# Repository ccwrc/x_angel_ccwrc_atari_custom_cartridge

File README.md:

## PCB fit to standard Atari XEGS (Taiwan), Warner and Sikor_Soft cases 

Details, manual, cookbook: [AtariOnline (Polish)](http://atarionline.pl/forum/comments.php?DiscussionID=4245&page=1#Item_0)      
Or auto translated to English: [AtariOnline (English - auto-translated)](https://atarionline-pl.translate.goog/forum/comments.php?DiscussionID=4245&page=1&_x_tr_sch=http&_x_tr_sl=pl&_x_tr_tl=en&_x_tr_hl=pl&_x_tr_pto=wapp#Item_0)      
The cartridge has been successfully tested with Atari 600XL, 800XL, 65XE, 130XE, 800XE and 65XE with memory expansion.    

## Where to Buy Cases       

Compatible cases are available for purchase through: [Sikor_Soft PL](http://sikorsoft.waw.pl/obudowy-do-cartridge-y/) or [Sikor_Soft Worldwide](http://sikorsoft.waw.pl/en/cartridge-cases/)

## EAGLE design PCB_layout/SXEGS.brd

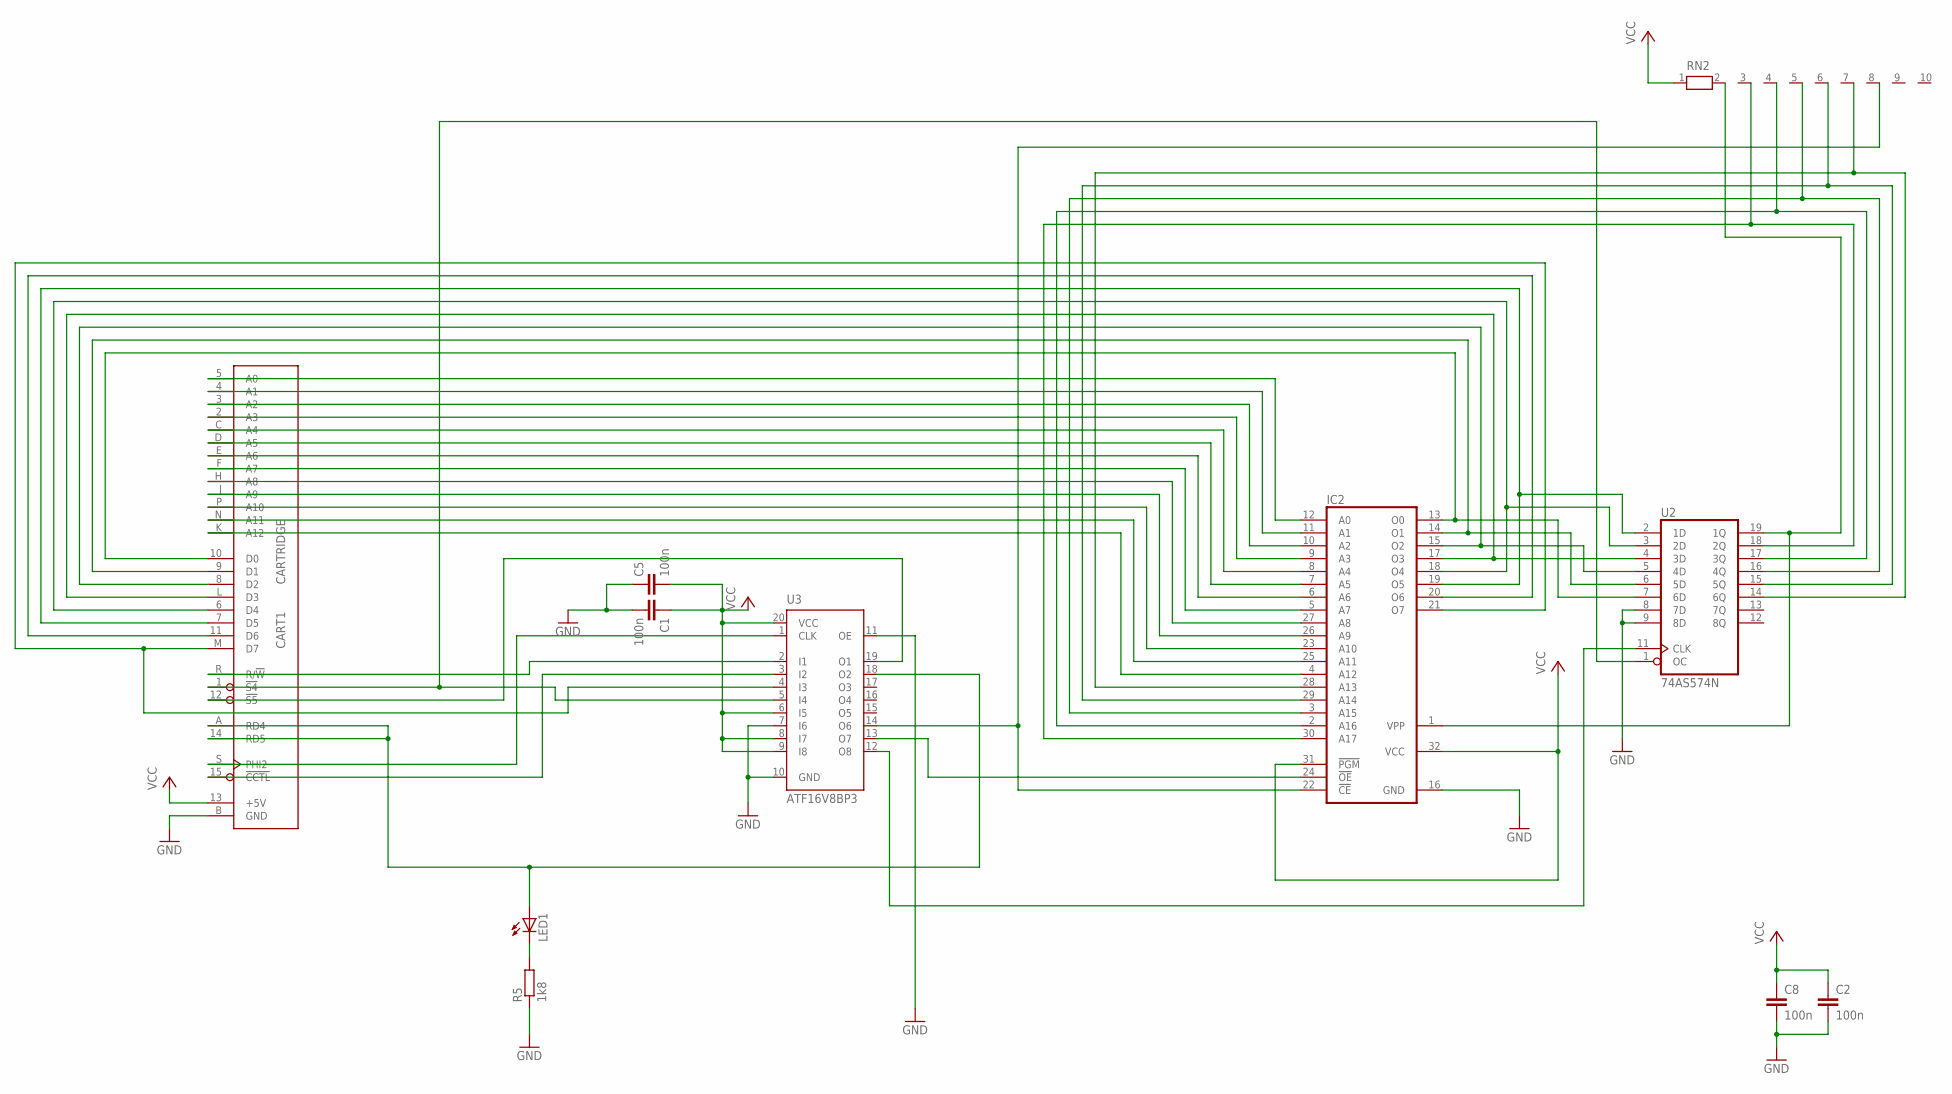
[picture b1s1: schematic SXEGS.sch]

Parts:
C1: 100n; C050-024X044
C2, C5, C8: 100n; C0805
CART1: CARTRIDGE
IC2: 27C2001D; DIL32
LED1: LEDCHIP-LED0805; CHIP-LED0805
R5: 1k8; R0805
RN2: RN09; RN-10
U2: 74AS574N; DIL20
U3: ATF16V8BP3; DIL20

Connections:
GND: C1.2, C2.2, C5.1, C8.2, CART1.B (GND), IC2.16 (GND), R5.1, U2.8 (7D), U2.9 (8D), U2.10 (GND), U3.7 (I6), U3.10 (GND), U3.11 (OE)
unnamed: LED1.C, R5.2
unnamed: IC2.30 (A17), RN2.3, U2.18 (2Q)
unnamed: CART1.R (R/!W), U3.2 (I1)
unnamed: CART1.14 (RD5), CART1.A (RD4), LED1.A, U3.18 (O2)
unnamed: IC2.1 (VPP), RN2.2, U2.19 (1Q)
unnamed: CART1.15 (!CCTL), U3.3 (I2)
unnamed: CART1.S (PHI2), U3.1 (CLK)
unnamed: CART1.1 (!S4), U2.1 (OC), U3.5 (I4)
unnamed: CART1.12 (!S5), U3.19 (O1)
unnamed: IC2.22 (!CE), RN2.8, U3.14 (O6)
unnamed: IC2.24 (!OE), U3.13 (O7)
unnamed: U2.11 (CLK), U3.12 (O8)
unnamed: CART1.10 (D0), IC2.13 (O0), U2.7 (6D)
unnamed: CART1.9 (D1), IC2.14 (O1), U2.6 (5D)
unnamed: CART1.8 (D2), IC2.15 (O2), U2.5 (4D)
unnamed: CART1.L (D3), IC2.17 (O3), U2.4 (3D)
unnamed: CART1.6 (D4), IC2.18 (O4), U2.3 (2D)
unnamed: CART1.7 (D5), IC2.19 (O5), U2.2 (1D)
unnamed: CART1.11 (D6), IC2.20 (O6)
unnamed: CART1.M (D7), IC2.21 (O7), U3.4 (I3)
unnamed: CART1.5 (A0), IC2.12 (A0)
unnamed: CART1.4 (A1), IC2.11 (A1)
unnamed: CART1.3 (A2), IC2.10 (A2)
unnamed: CART1.2 (A3), IC2.9 (A3)
unnamed: CART1.C (A4), IC2.8 (A4)
unnamed: CART1.D (A5), IC2.7 (A5)
unnamed: CART1.E (A6), IC2.6 (A6)
unnamed: CART1.F (A7), IC2.5 (A7)
unnamed: CART1.H (A8), IC2.27 (A8)
unnamed: CART1.J (A9), IC2.26 (A9)
unnamed: CART1.P (A10), IC2.23 (A10)
unnamed: CART1.N (A11), IC2.25 (A11)
unnamed: CART1.K (A12), IC2.4 (A12)
unnamed: IC2.28 (A13), RN2.7, U2.14 (6Q)
unnamed: IC2.29 (A14), RN2.6, U2.15 (5Q)
unnamed: IC2.3 (A15), RN2.5, U2.16 (4Q)
unnamed: IC2.2 (A16), RN2.4, U2.17 (3Q)
VCC: C1.1, C2.1, C5.2, C8.1, CART1.13 (+5V), IC2.31 (!PGM), IC2.32 (VCC), RN2.1, U2.20 (VCC), U3.6 (I5), U3.8 (I7), U3.9 (I8), U3.20 (VCC)

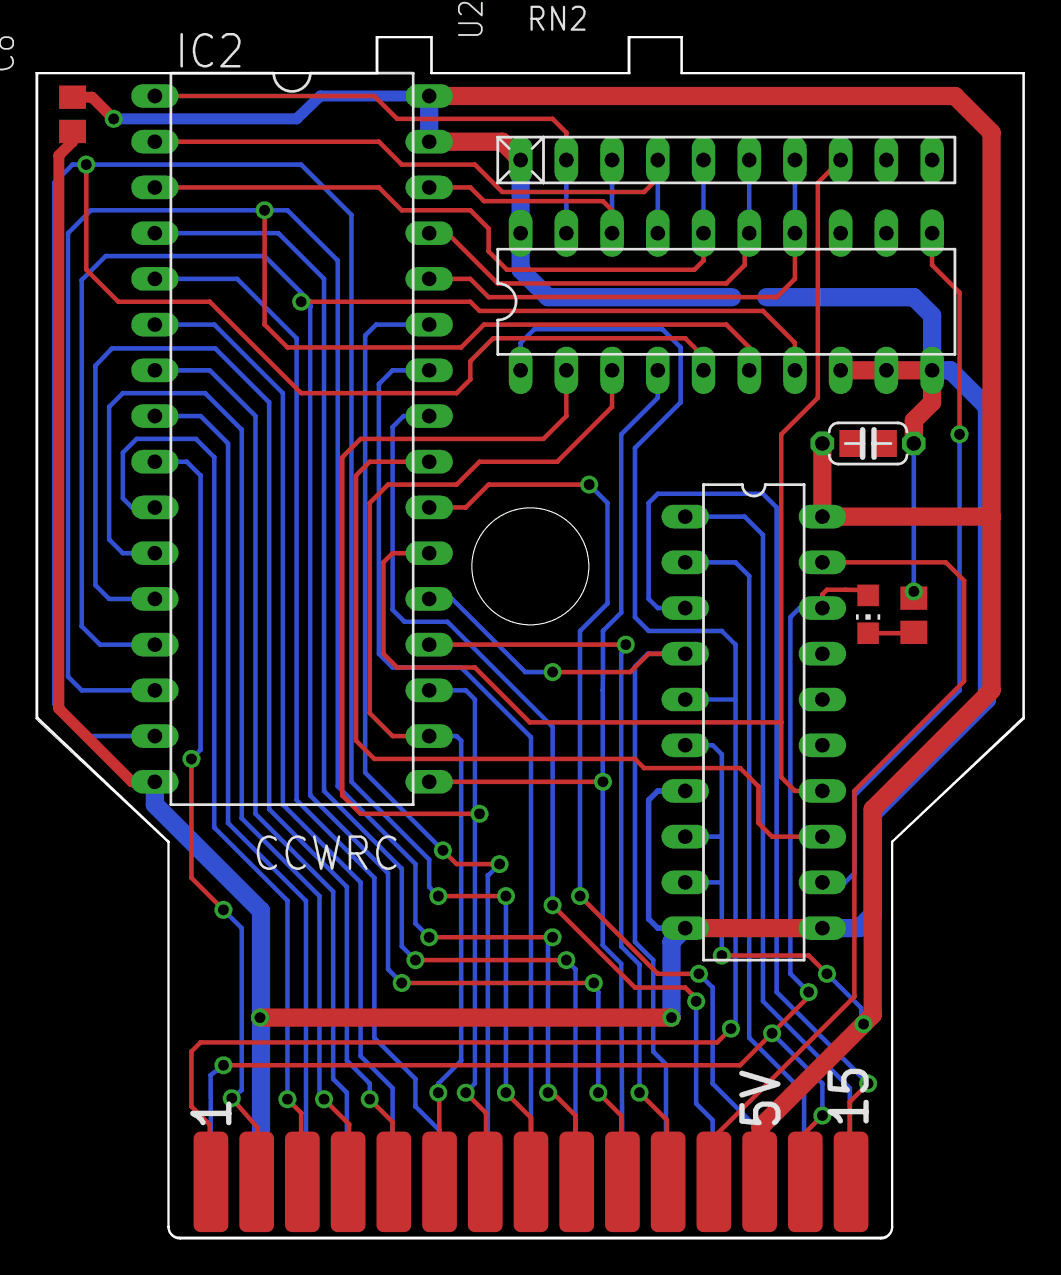
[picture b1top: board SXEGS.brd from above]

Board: 2 copper layers, 54.8 x 66.7 mm, 11 parts (1 on the bottom side), 39 nets.

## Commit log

2017-09-12 add pcb scheme
2017-09-12 readme update
2017-09-12 another readme update
2025-01-09 updated readme and gitignore

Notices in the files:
parts and their libraries:
Atari Corp Cartridge: Copyright (c) 2010
Copyright (c) 2009
This library is licensed under the
Creative Commons Attribution 3.0 United States License.
